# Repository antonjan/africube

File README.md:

# africube is the repository of a linear satellite transponder. (AMSATSA)
# pcb
<br>
# Project Status.
This project TX PCB is compleet and testing will start now. 10 September 2019
Transponder is now working propely and CW and APRS telemetry is also working.
Oustanding is sensor reading. 16 Jan 2020
# Link Budget

It is necessary that our beacon’s signal be able to reach the antenna at our ground station.  
The beacon will transmit at 145.850 MHz.<br>  
Using the free space model, we can calculate the maximum path loss:<br>
### Maximum Path Loss = 32.4 dB + 20 log(dkm) dB + 20 log(fMHz) dB=32.4 dB + 20 log(8000) dB + 20 log(140) dB=144.86 dB<br>
Our transmission power will be 200 mW, which in dBm is 23 (30 + 10 log(0.1)) <br>
The feeder loss for ourtransmitter will be quite low, since the radio is close to the antenna on the cubeSAT. <br>
We will assume this loss is about 0.2 dB and that the antenna’s gain is about 2 dI (which is reasonable for a whip antenna ona cubeSAT), so our effective isotropic radiated power should be about 24.6 dBm <br>
### EIRP = Transmission Power−Feeder Loss + Antenna Gain=23 dB−0.2 dB + 2 dB=25.8 dB<br>
To calculate the quality of our received signal we also need to know the polarization mismatch, the ionosphericpropagation mismatch, the antenna’s gain, the antenna’s feeder loss, and the noise floor.<br>
We will let thesebe 3 dB, 1 dB, 12.34 dBI, 5.5 dB, and−130 dBm, respectively.<br>
### Max Range Received Signal =  EIRP−Max Path Loss−Mismatch Loss − Propagation Loss +Antenna Gain−Feeder Loss= 25.8dB − 144.86 dB−3 dB−1 dB + 12.34 dB−5.5 dB=−117.22 dB<br>
### Quality Assessment    =    Max Range Received Signal−Noise Floor=−120.22 dB−(−130 dB)=    12.78 dBSo, at the ground station, we should expect a SNR of about 9.78 dB.<br>

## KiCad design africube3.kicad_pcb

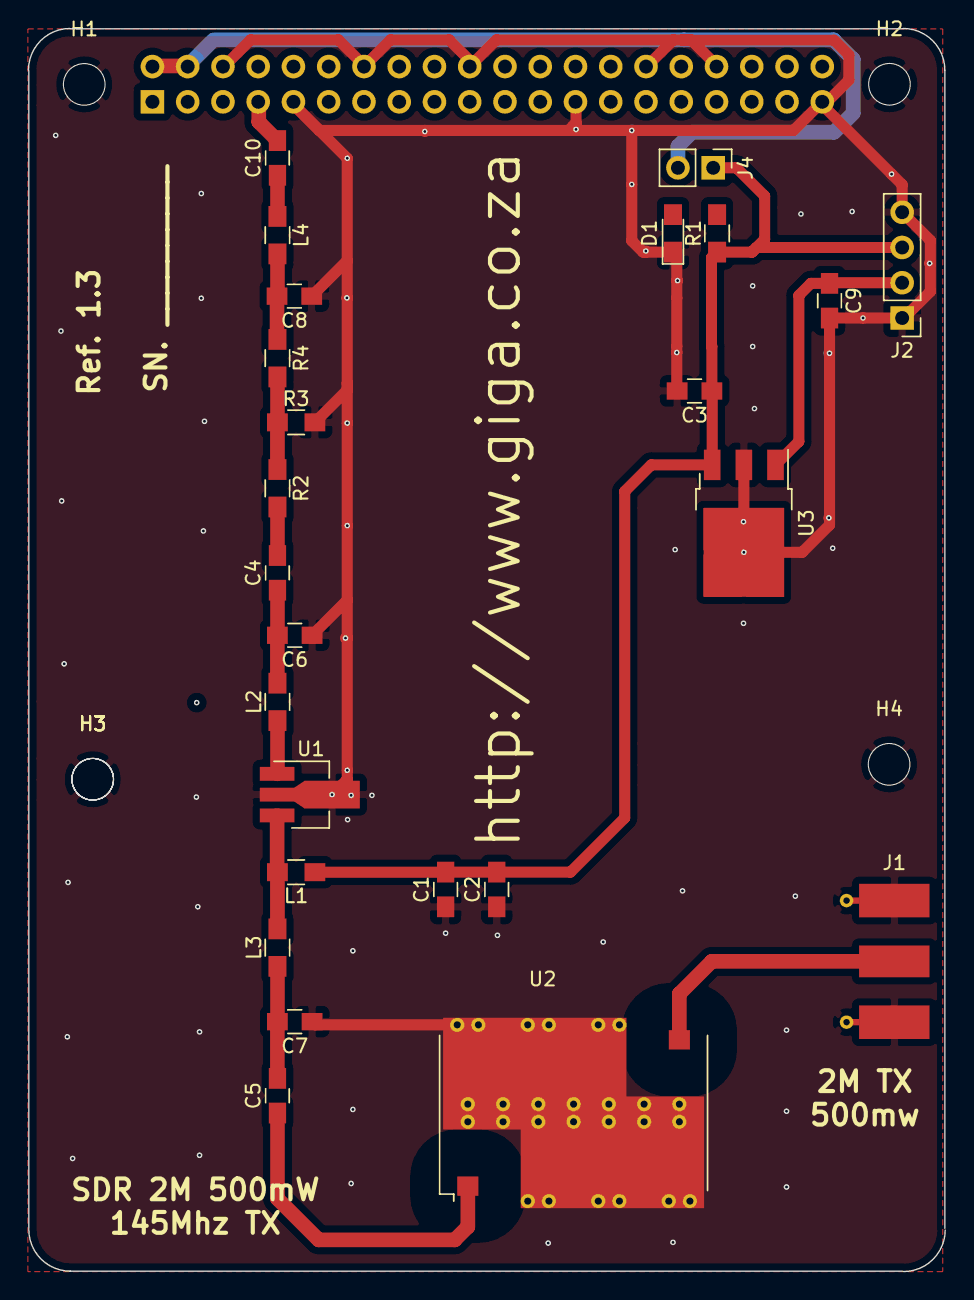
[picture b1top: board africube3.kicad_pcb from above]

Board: 2 copper layers, 66.1 x 89.6 mm, 34 parts (1 on the bottom side), 16 nets.

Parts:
C1: 100nF; C_0805_HandSoldering
C2, C4, C5, C10: 100pF; C_0805_HandSoldering
C3, C9: 4.7uF 16V; C_0805_HandSoldering
C6: 12pF; C_0805_HandSoldering
C7: 22pF; C_0805_HandSoldering
C8: 10pF; C_0805_HandSoldering
D1: LED; LED_0805_HandSoldering
H1, H2, H3, H3#2, H3#3, H3#4, H4: 3mm_hole; MountingHole_3mm
J1: SMA Edge FM; Molex_SMA_Jack_Edge_Mount
J2: Conn_01x04; Socket_Strip_Straight_1x04_Pitch2.54mm
J3: PinSocket_2x20_P2.54mm_Vertical
J3#2: RPi_GPIO; PinSocket_2x20_P2.54mm_Vertical_SMD
J4: Conn_01x02; Pin_Header_Straight_1x02_Pitch2.54mm
L1: 12nH; R_0805_HandSoldering
L2, L3, L4: 0; R_0805_HandSoldering
R1: 330; R_0805_HandSoldering
R2, R4: 0; R_0805_HandSoldering
R3: OC; R_0805_HandSoldering
U1: TQP7M9105; SOT-89-3_Handsoldering
U2: SXBP-150+; Mini-Circuits_HF1139_LandPatternPL-230
U3: BA178M05FP-E2; TO-252-3_TabPin4

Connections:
+5V: C1.2, C2.2, C3.1, J2.3, J4.1, L1.1, R1.1, U3.3
GND: C1.1, C2.1, C3.2, C6.1, C7.1, C8.1, C9.2, D1.1, H1.1, H2.1, H3.1, H3#2.1, H3#3.1, H3#4.1, H4.1, J1.2, J2.1, J2.4, J3#2.6, J3#2.9, J3#2.14, J3#2.20, J3#2.25, J3#2.30, J3#2.34, J3#2.39, R3.2, U1.2, U2.2, U2.3, U2.4, U2.5, U2.6, U2.7, U3.2, U3.4
unnamed: C4.1, C6.2, L2.2
unnamed: C4.2, R2.2
unnamed: C5.1, U2.1
unnamed: C5.2, C7.2, L3.1
unnamed: C8.2, L4.2, R4.1
unnamed: C9.1, J2.2, U3.1
unnamed: C10.1, L4.1
unnamed: C10.2, J3#2.7
unnamed: D1.2, R1.2
unnamed: J1.1, U2.8
unnamed: J3#2.2, J3#2.4, J4.2
unnamed: L1.2, L3.2, U1.3
unnamed: L2.1, U1.1
unnamed: R2.1, R3.1, R4.2

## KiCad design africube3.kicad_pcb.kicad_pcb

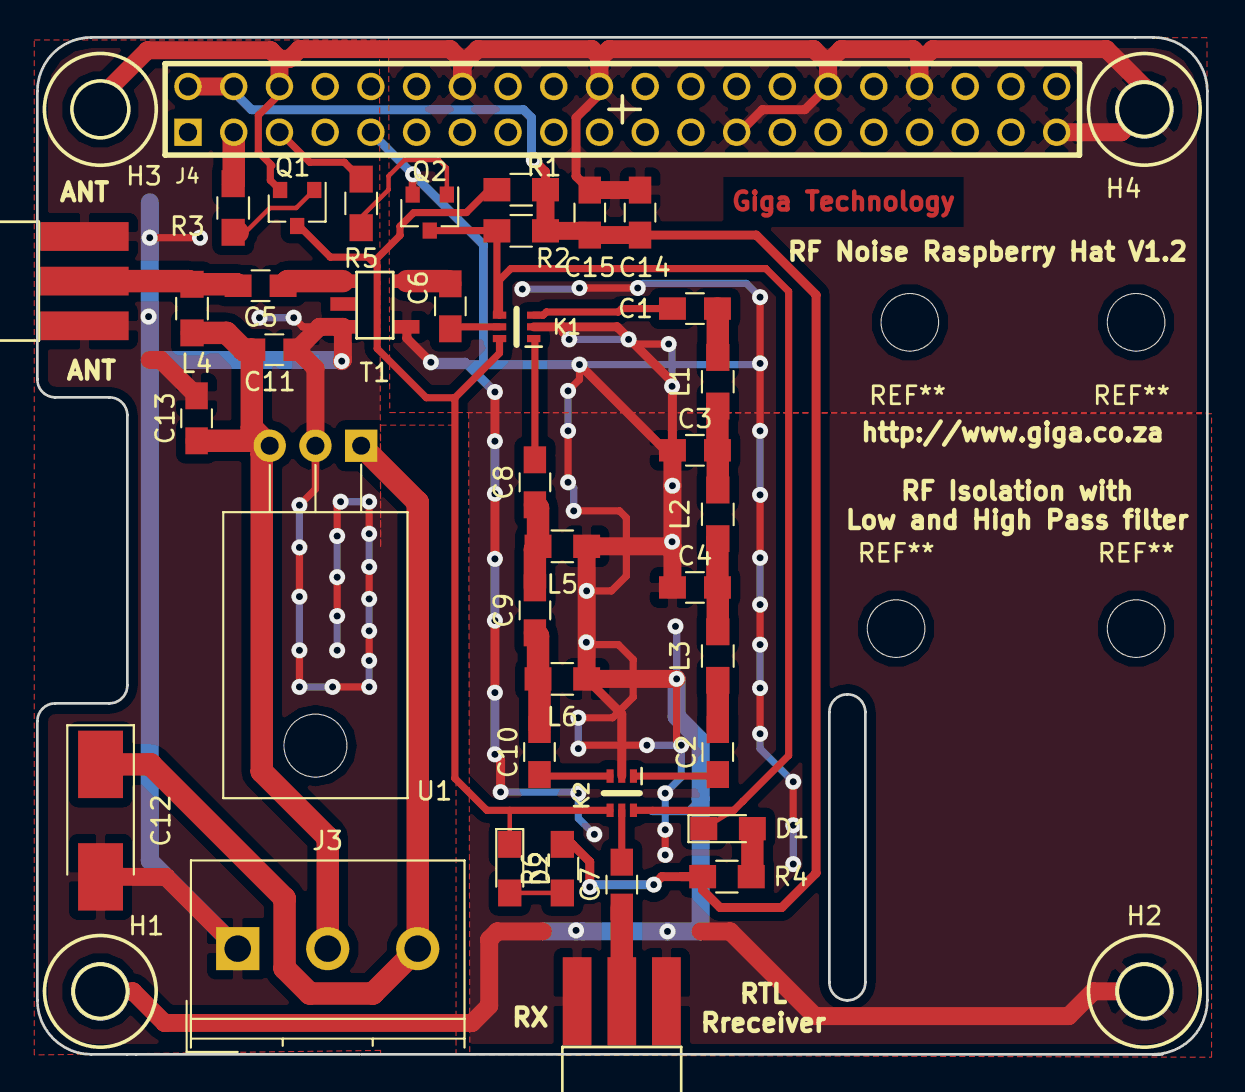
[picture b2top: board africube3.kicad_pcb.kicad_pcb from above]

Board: 2 copper layers, 65.0 x 56.5 mm, 43 parts (0 on the bottom side), 29 nets.

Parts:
C1, C2, C5, C6, C7, C11, C14: 100nF; C_0805_HandSoldering
C3, C4: 360pF; C_0805_HandSoldering
C8, C10: 390pF; C_0805_HandSoldering
C9: 120pF; C_0805_HandSoldering
C12: 47uF 16V; CP_Tantalum_Case-C_EIA-6032-28_Hand
C13, C15: 4.7uF 16V; C_0805_HandSoldering
D1, D2: LED; LED_0805_HandSoldering
H1, H2, H3, H4: Conn_01x01; MountingHole_3.2mm_M3
J1, J2: Conn_Coaxial; SMA_Edge
J3: Conn_01x03; TerminalBlock_Philmore_TB133_03x5mm_Straight
J4: Raspberry_Pi_2_3; PIN_ARRAY_20X2
K1, K2: MASWSS0115; SC-70-6
L1, L3: 330nH; L_0805_HandSoldering
L2: 1.1uH; L_0805_HandSoldering
L4: 10uH; L_0805_HandSoldering
L5, L6: 360nH; L_0805_HandSoldering
Q1, Q2: BC847; SOT-23
R1, R2, R4, R6: 250; R_0805_HandSoldering
R3, R5: 1k2; R_0805_HandSoldering
T1: MABA-009180-500MHz_1P_1S; SM22
U1: L7812; TO-220_Horizontal

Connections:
+5V: C14.1, C15.1, J4.2, J4.4, R1.2, R2.2, R4.2, R6.2
GND: C3.1, C4.1, C14.2, C15.2, H1.1, H2.1, H3.1, H4.1, J2.2, J4.6, J4.9, J4.14, J4.20, J4.25, J4.30, J4.34, J4.39, K1.2, K2.2, L5.1, L6.1, Q1.2, Q2.2, T1.4
GNDA: C11.2, C12.2, C13.2, J1.2, J3.1, T1.3, U1.2
unnamed: C1.1, L1.2
unnamed: C1.2, K1.3
unnamed: C2.1, K2.1
unnamed: C2.2, L3.1
unnamed: C3.2, L1.1, L2.2
unnamed: C4.2, L2.1, L3.2
unnamed: C5.1, T1.1
unnamed: C5.2, J1.1, L4.1
unnamed: C6.1, K1.5
unnamed: C6.2, T1.5
unnamed: C7.1, J2.1
unnamed: C7.2, K2.5
unnamed: C8.1, C9.2, L5.2
unnamed: C8.2, K1.1
unnamed: C10.1, K2.3
unnamed: C9.1, C10.2, L6.2
unnamed: C11.1, C13.1, J3.2, L4.2, U1.3
unnamed: C12.1, J3.3, U1.1
unnamed: D1.1, K1.4, K2.6, Q2.3, R2.1
unnamed: D1.2, R4.1
unnamed: D2.1, K1.6, K2.4, Q1.3, R1.1
unnamed: D2.2, R6.1
unnamed: J4.3, R3.1
unnamed: J4.5, R5.2
unnamed: Q1.1, R3.2
unnamed: Q2.1, R5.1

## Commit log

2019-07-12 first code load
2019-07-12 adding Readme
2019-07-12 pcb placement
2019-07-16 Adding pc104 footprint
2019-07-17 adding pc104
2019-07-17 adding Compute Module_doc
2019-07-18 adding pi Layout
2019-07-18 starting to layout pcb
2019-07-23 adding directional copler
2019-08-14 placing board
2019-08-26 Making pcb Bigger
2019-08-28 removing power detector
2019-08-29 removed power detection
2019-09-04 layout done need to do groundplanes
2019-09-05 added groundplane
2019-09-06 Created gerber files
2019-09-10 adding project status
2020-01-16 adding rf amp docks
2020-01-16 adding Power budget and amp doc
2020-01-16 Adding Link Budget
2020-01-16 fix spelling
2020-03-02 adding formatting
2020-03-02 adding formatiing
2020-03-05 adding pcb image
2020-03-12 upgrade modules to new cad
2022-01-28 updated the pcd file to africube 4 by readding inductor L5
2022-07-20 fixing tracks that was missing
